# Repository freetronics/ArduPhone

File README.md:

Freetronics ArduPhone
=====================
Copyright 2013 Freetronics Pty Ltd www.freetronics.com  

The ArduPhone is an Arduino compatible board with onboard
GSM module, OLED display, matrix keypad, and battery
charger.

Features:

 * Micro-USB connector for charging and programming
 * Overlay guide where you need it (both top and bottom)
 * Mounting holes and power pads

More info at:

  http://www.freetronics.com.au/phone

INSTALLATION
------------
The design is saved as an EAGLE project. EAGLE PCB design software is
available from www.cadsoftusa.com free for non-commercial use. To use
this project download it and place the directory containing these files
into the "eagle" directory on your computer. Then open EAGLE and
navigate to Projects -> eagle -> PHONE.

DISTRIBUTION
------------
The specific terms of distribution of this project are governed by the
license referenced below.

LICENSE
-------
Licensed under the TAPR Open Hardware License (www.tapr.org/OHL).
The "license" folder within this repository also contains a copy of
this license in plain text format.

CREDITS
-------
The ArduPhone was designed by Jonathan Oxer (jon@freetronics.com)
inspired by previous work by David Mellis.

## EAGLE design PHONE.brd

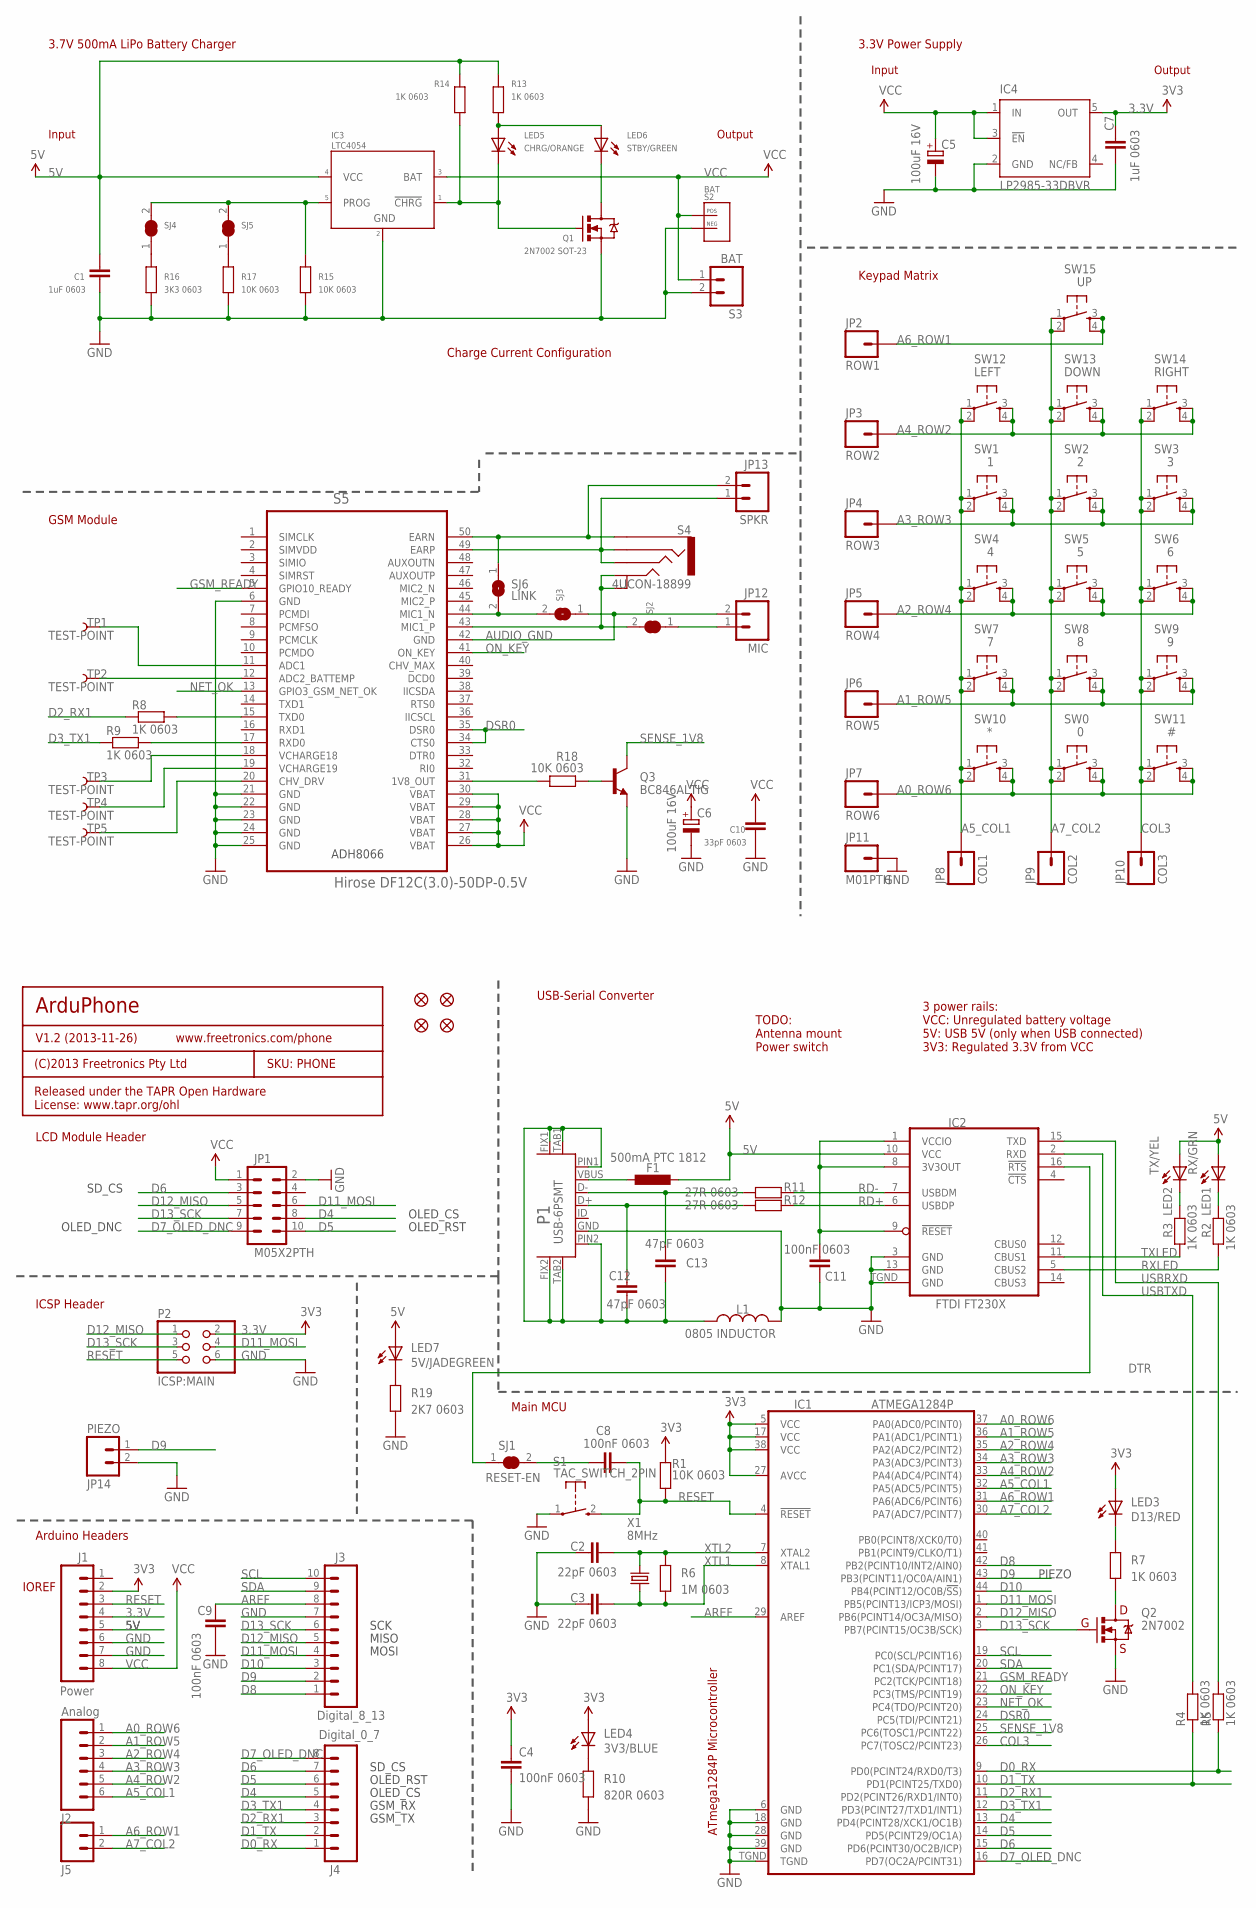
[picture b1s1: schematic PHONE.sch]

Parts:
C1, C7: 1uF 0603; 0603
C2, C3: 22pF 0603; 0603
C4, C8, C9, C11: 100nF 0603; 0603
C5, C6: 100uF 16V; PANASONIC_D
C10: 33pF 0603; 0603@1
C12, C13: 47pF 0603; C0603
F1: 500mA PTC 1812; L1812
IC1: ATMEGA1284P; QFN-44M1
IC2: FT230X; QFN-16
IC3: LTC4054; SOT23-5
IC4: LP2985-33DBVR; TEXAS_SOT23-DBV
J1: Power; 1X08
J2: Analog; 1X06
J3: Digital_8_13; 1X10
J4: Digital_0_7; 1X08
J5: M02PTH; 1X02
JP1: M05X2PTH; AVR_ICSP
JP2: ROW1; 1X01
JP3: ROW2; 1X01
JP4: ROW3; 1X01
JP5: ROW4; 1X01
JP6: ROW5; 1X01
JP7: ROW6; 1X01
JP8: COL1; 1X01
JP9: COL2; 1X01
JP10: COL3; 1X01
JP11: M01PTH; 1X01
JP12: MIC; 1X02
JP13: SPKR; 1X02
JP14: PIEZO; 1X02
L1: 0805 INDUCTOR; 0805-LARGE
LED1: RX/GRN; LED-0603
LED2: TX/YEL; LED-0603
LED3: D13/RED; LED-0603
LED4: 3V3/BLUE; LED-0603
LED5: CHRG/ORANGE; LED-0603
LED6: STBY/GREEN; LED-0603
LED7: 5V/JADEGREEN; LED-0603
P1: USB-6PSMT; USB-MICROB-MB05PMXX
P2: ICSP:MAIN; 2X03
Q1: 2N7002 SOT-23; SOT23-3
Q2: 2N7002; SOT23-3
Q3: BC846ALTIG; SOT23-3
R1, R15, R17, R18: 10K 0603; 0603
R2, R3, R4, R5, R7, R8, R9, R13, R14: 1K 0603; 0603
R6: 1M 0603; 0603
R10: 820R 0603; 0603
R11, R12: 27R 0603; 0603
R16: 3K3 0603; 0603
R19: 2K7 0603; 0603
S1: TAC_SWITCH_2PIN; TACTILE_SWITCH_SMD_2PIN_TINY
S2: BAT; JST-2MM-TH-RA
S3: BAT; 1X02
S4: 4UCON-18899
S5: Hirose DF12C(3.0)-50DP-0.5V; ADH8066
SJ1: RESET-EN; SJC
SJ2, SJ4, SJ5: SJCN; SJC
SJ3: SJ
SJ6: LINK; SJ
SW0: 0; TACTILE-PTH
SW1: 1; TACTILE-PTH
SW2: 2; TACTILE-PTH
SW3: 3; TACTILE-PTH
SW4: 4; TACTILE-PTH
SW5: 5; TACTILE-PTH
SW6: 6; TACTILE-PTH
SW7: 7; TACTILE-PTH
SW8: 8; TACTILE-PTH
SW9: 9; TACTILE-PTH
SW10: *; TACTILE-PTH
SW11: #; TACTILE-PTH
SW12: LEFT; TACTILE-PTH
SW13: DOWN; TACTILE-PTH
SW14: RIGHT; TACTILE-PTH
SW15: UP; TACTILE-PTH
TP1, TP2, TP3, TP4, TP5: TEST-POINT; PAD.02X.02
U$5, U$6, U$7, U$14: FIDUCIAL1X2.5; FIDUCIAL-1X2.5
X1: 8MHz; HC49U-V

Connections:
3.3V: C4.1, C7.2, IC1.5 (VCC), IC1.17 (VCC), IC1.27 (AVCC), IC1.38 (VCC), IC4.5 (OUT), J1.2, J1.4, LED3.A, LED4.A, P2.2, R1.2
5V: C1.2, F1.2, IC2.10 (VCC), IC3.4 (VCC), J1.5, LED1.A, LED2.A, LED7.A, R13.1, R14.1
A0_ROW6: IC1.37 (PA0(ADC0/PCINT0)), J2.1, JP7.1, SW0.3, SW0.4, SW10.3, SW10.4, SW11.3, SW11.4
A1_ROW5: IC1.36 (PA1(ADC1/PCINT1)), J2.2, JP6.1, SW7.3, SW7.4, SW8.3, SW8.4, SW9.3, SW9.4
A2_ROW4: IC1.35 (PA2(ADC2/PCINT2)), J2.3, JP5.1, SW4.3, SW4.4, SW5.3, SW5.4, SW6.3, SW6.4
A3_ROW3: IC1.34 (PA3(ADC3/PCINT3)), J2.4, JP4.1, SW1.3, SW1.4, SW2.3, SW2.4, SW3.3, SW3.4
A4_ROW2: IC1.33 (PA4(ADC4/PCINT4)), J2.5, JP3.1, SW12.3, SW12.4, SW13.3, SW13.4, SW14.3, SW14.4
A5_COL1: IC1.32 (PA5(ADC5/PCINT5)), J2.6, JP8.1, SW1.1, SW1.2, SW4.1, SW4.2, SW7.1, SW7.2, SW10.1, SW10.2, SW12.1, SW12.2
A6_ROW1: IC1.31 (PA6(ADC6/PCINT6)), J5.1, JP2.1, SW15.3, SW15.4
A7_COL2: IC1.30 (PA7(ADC7/PCINT7)), J5.2, JP9.1, SW0.1, SW0.2, SW2.1, SW2.2, SW5.1, SW5.2, SW8.1, SW8.2, SW13.1, SW13.2, SW15.1, SW15.2
AREF: C9.1, IC1.29 (AREF), J3.8
AUDIO_GND: JP12.2, S5.42 (GND), SJ3.1
COL3: IC1.26 (PC7(TOSC2/PCINT23)), JP10.1, SW3.1, SW3.2, SW6.1, SW6.2, SW9.1, SW9.2, SW11.1, SW11.2, SW14.1, SW14.2
D0_RX: IC1.9 (PD0(PCINT24/RXD0/T3)), J4.1, R5.1
D1_TX: IC1.10 (PD1(PCINT25/TXD0)), J4.2, R4.1
D2_RX1: IC1.11 (PD2(PCINT26/RXD1/INT0)), J4.3, R8.1
D3_TX1: IC1.12 (PD3(PCINT27/TXD1/INT1)), J4.4, R9.1
D4: IC1.13 (PD4(PCINT28/XCK1/OC1B)), J4.5, JP1.8
D5: IC1.14 (PD5(PCINT29/OC1A)), J4.6, JP1.10
D6: IC1.15 (PD6(PCINT30/OC2B/ICP)), J4.7, JP1.3
D7_OLED_DNC: IC1.16 (PD7(OC2A/PCINT31)), J4.8, JP1.9
D8: IC1.42 (PB2(PCINT10/INT2/AIN0)), J3.1
D9: IC1.43 (PB3(PCINT11/OC0A/AIN1)), J3.2, JP14.1
D10: IC1.44 (PB4(PCINT12/OC0B/!SS!)), J3.3
D11_MOSI: IC1.1 (PB5(PCINT13/ICP3/MOSI)), J3.4, JP1.6, P2.4
D12_MISO: IC1.2 (PB6(PCINT14/OC3A/MISO)), J3.5, JP1.5, P2.1
D13_SCK: IC1.3 (PB7(PCINT15/OC3B/SCK)), J3.6, JP1.7, P2.3, Q2.1 (G)
DSR0: IC1.24 (PC5(TDI/PCINT21)), S5.34 (CTS0), S5.35 (DSR0)
DTR: IC2.16 (!RTS), SJ1.1
GND: C1.1, C2.1, C3.1, C4.2, C5.-, C6.-, C7.1, C9.2, C10.1, C11.2, IC1.6 (GND), IC1.18 (GND), IC1.28 (GND), IC1.39 (GND), IC1.TGND, IC2.3 (GND), IC2.13 (GND), IC2.TGND (GND), IC3.2 (GND), IC4.2 (GND), J1.6, J1.7, J3.7, JP1.2, JP11.1, JP14.2, L1.2, P1.GND, P2.6, Q1.2 (S), Q2.2 (S), Q3.2 (E), R10.1, R15.2, R16.2, R17.2, R19.1, S1.1, S2.NEG, S3.2, S5.6 (GND), S5.21 (GND), S5.22 (GND), S5.23 (GND), S5.24 (GND), S5.25 (GND)
GSM_READY: IC1.21 (PC2(TCK/PCINT18)), S5.5 (GPIO10_READY)
unnamed: C8.1, SJ1.2
unnamed: C11.1, IC2.1 (VCCIO), IC2.8 (3V3OUT), IC2.9 (!RESET)
unnamed: C12.2, C13.2, L1.1, P1.FIX1, P1.FIX2, P1.PIN1, P1.PIN2, P1.TAB1, P1.TAB2
unnamed: LED3.C, R7.2
unnamed: LED6.C, Q1.3 (D)
unnamed: Q2.3 (D), R7.1
unnamed: LED7.C, R19.2
unnamed: LED5.A, LED6.A, R13.2
unnamed: S4.2A, S4.2B, S5.43 (MIC1_P), SJ2.2
unnamed: IC3.1 (!CHRG), LED5.C, Q1.1 (G), R14.2
unnamed: LED1.C, R2.2
unnamed: IC3.5 (PROG), R15.1, SJ4.2, SJ5.2
unnamed: LED2.C, R3.2
unnamed: LED4.C, R10.2
unnamed: Q3.1 (B), R18.1
unnamed: C12.1, P1.D+, R12.2
unnamed: C13.1, P1.D-, R11.2
unnamed: S5.44 (MIC1_N), SJ3.2, SJ6.2
unnamed: JP13.2, S4.1, S5.50 (EARN), SJ6.1
unnamed: JP13.1, S4.3, S4.4, S5.49 (EARP)
unnamed: R8.2, S5.15 (TXD0)
unnamed: R9.2, S5.17 (RXD0)
unnamed: S5.18 (VCHARGE18), TP3.P$1
unnamed: S5.19 (VCHARGE19), TP4.P$1
unnamed: S5.20 (CHV_DRV), TP5.P$1
unnamed: R18.2, S5.31 (1V8_OUT)
unnamed: JP12.1, SJ2.1
unnamed: S5.11 (ADC1), TP1.P$1
unnamed: S5.12 (ADC2_BATTEMP), TP2.P$1
unnamed: R16.1, SJ4.1
unnamed: R17.1, SJ5.1
unnamed: F1.1, P1.VBUS
NET_OK: IC1.23 (PC4(TDO/PCINT20)), S5.13 (GPIO3_GSM_NET_OK)
ON_KEY: IC1.22 (PC3(TMS/PCINT19)), S5.41 (ON_KEY)
RD+: IC2.6 (USBDP), R12.1
RD-: IC2.7 (USBDM), R11.1
RESET: C8.2, IC1.4 (!RESET), J1.3, P2.5, R1.1, S1.2 (S)
RXLED: IC2.5 (CBUS2), R2.1
SCL: IC1.19 (PC0(SCL/PCINT16)), J3.10
SDA: IC1.20 (PC1(SDA/PCINT17)), J3.9
SENSE_1V8: IC1.25 (PC6(TOSC1/PCINT22)), Q3.3 (C)
TXLED: IC2.11 (CBUS1), R3.1
USBRXD: IC2.15 (TXD), R5.2
USBTXD: IC2.2 (RXD), R4.2
VCC: C5.+, C6.+, C10.2, IC3.3 (BAT), IC4.1 (IN), IC4.3 (!EN), J1.8, JP1.1, S2.POS, S3.1, S5.26 (VBAT), S5.27 (VBAT), S5.28 (VBAT), S5.29 (VBAT), S5.30 (VBAT)
XTL1: C3.2, IC1.8 (XTAL1), R6.1, X1.1
XTL2: C2.2, IC1.7 (XTAL2), R6.2, X1.2

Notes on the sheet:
ArduPhone
V1.2 (2013-11-26)
SKU: PHONE
(C)2013 Freetronics Pty Ltd
Released under the TAPR Open Hardware License: www.tapr.org/ohl
www.freetronics.com/phone
IOREF
ATmega1284P Microcontroller
3 power rails: VCC: Unregulated battery voltage 5V: USB 5V (only when USB connected) 3V3: Regulated 3.3V from VCC
OLED_DNC
SD_CS
OLED_CS
OLED_RST
TODO: Antenna mount Power switch
Output
Input
3.7V 500mA LiPo Battery Charger
3.3V Power Supply
Keypad Matrix
GSM Module
LCD Module Header
USB-Serial Converter
Main MCU
Arduino Headers
ICSP Header
SCK
MISO
MOSI
GSM_RX
GSM_TX
Charge Current Configuration
ADH8066
PIEZO

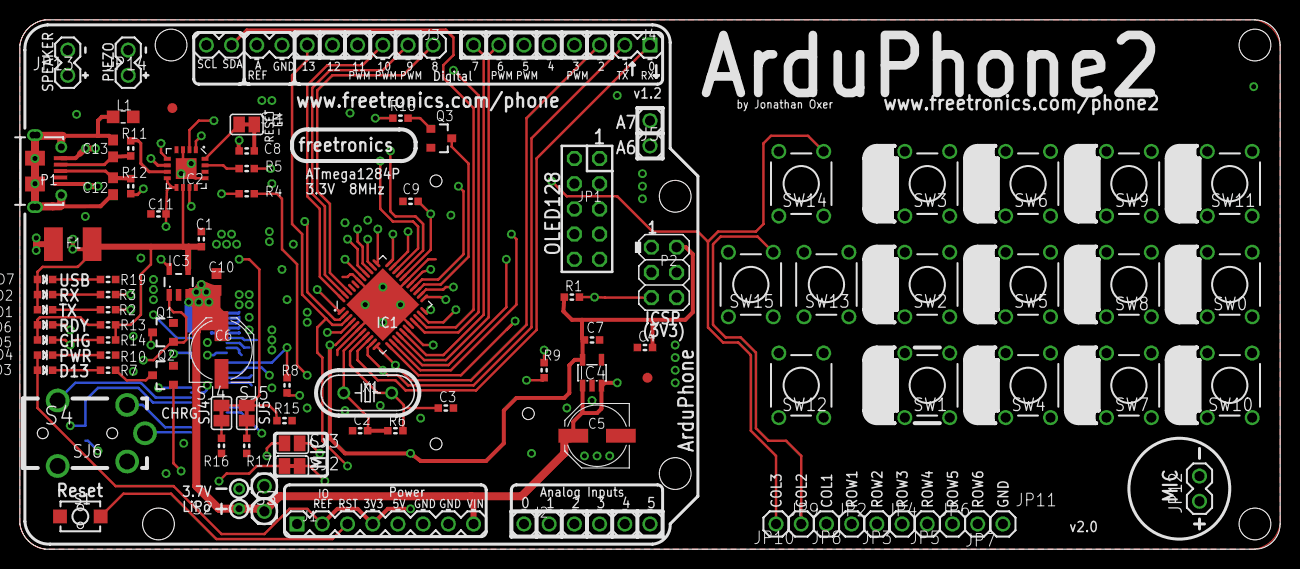
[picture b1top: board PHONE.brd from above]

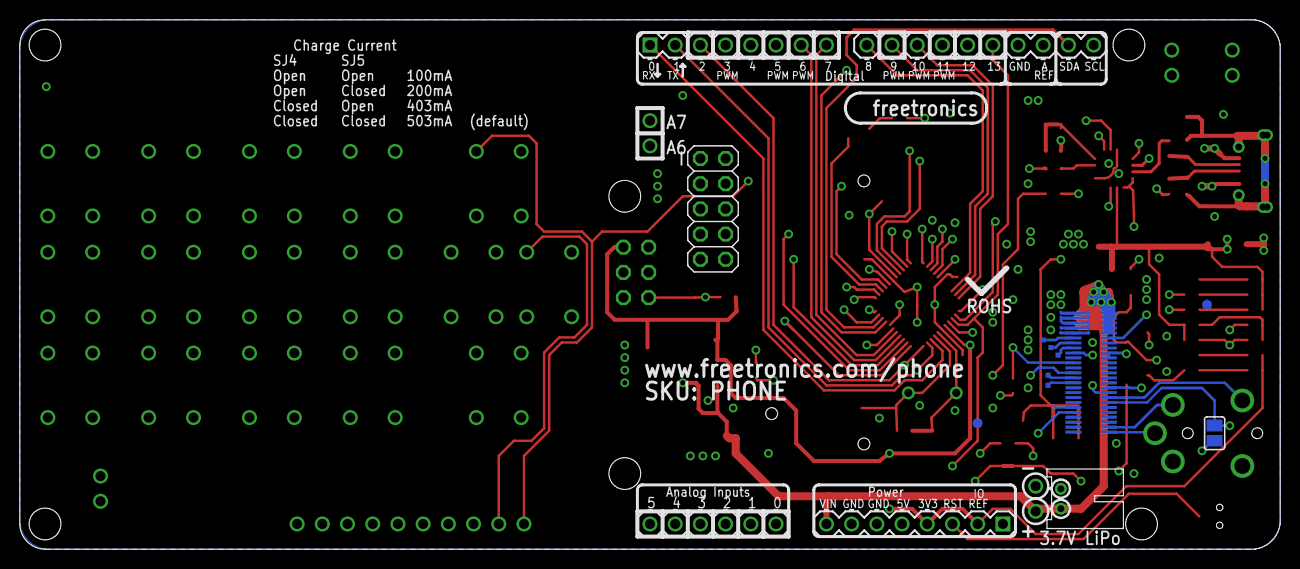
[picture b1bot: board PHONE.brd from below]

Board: 4 copper layers, 127.0 x 53.3 mm, 106 parts (11 on the bottom side), 78 nets.

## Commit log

2013-10-28 Initial project import
2013-10-31 v1.0 release
2013-11-26 v1.1 release: separated AUDIO_GND from system GND
2013-11-26 Switched to 4 layers and rerouted for v1.2 release
2014-03-17 Reconciled schematic and layout using common parts
2018-03-28 Updated designators

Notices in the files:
parts and their libraries:
freetronics-original: Licensing: CC v3.0 Share-Alike You are welcome to use this library for commercial purposes.
